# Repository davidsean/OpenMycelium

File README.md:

# OpenMycelium
Yet another Raspberry Pi project: an IoT environmental controller for mycelium growth and fruiting.
This is a open-hardware and open-source DIY project.
It can be used to control the conditions for spawn incubation, mycelium growth and for fruiting.

# Project status
This is still in its infancy. Nothing works yet, so please join the OpenIoT discord server (https://discord.com/invite/Ft229PDrxF) to contribute.

# Hardware
It comprises of a control board with temperature and humidity sensors, that can actual a heater, fan (and ultrasonic mister), light.
All the sensors and actuators are optional, so you jsut need to buy/assemble what you need.

## GOAL (not done yet)
The KiCAD PCB is provided that takes the form of a Raspberry-pi hat.
It needs be populate with some through-hole components (so find someone with a soldering iron if you aren't sure of being able to do this).
The PCB is more or less modular so you dpn't need to fully assemble it with all the features if you don't need them.

# Sofware
The software runs on a Raspberry-Pi.

## Goal (not done yet)
Uses cloud-link to host a Firebase webserver as an interface.
Logs telemetry over MQTT, can choose control "growth recipes".

# dev
```bash
conda create -n openmycelium python=3.8
conda activate openmycelium
python3 -m pip install -r requirements.txt
```

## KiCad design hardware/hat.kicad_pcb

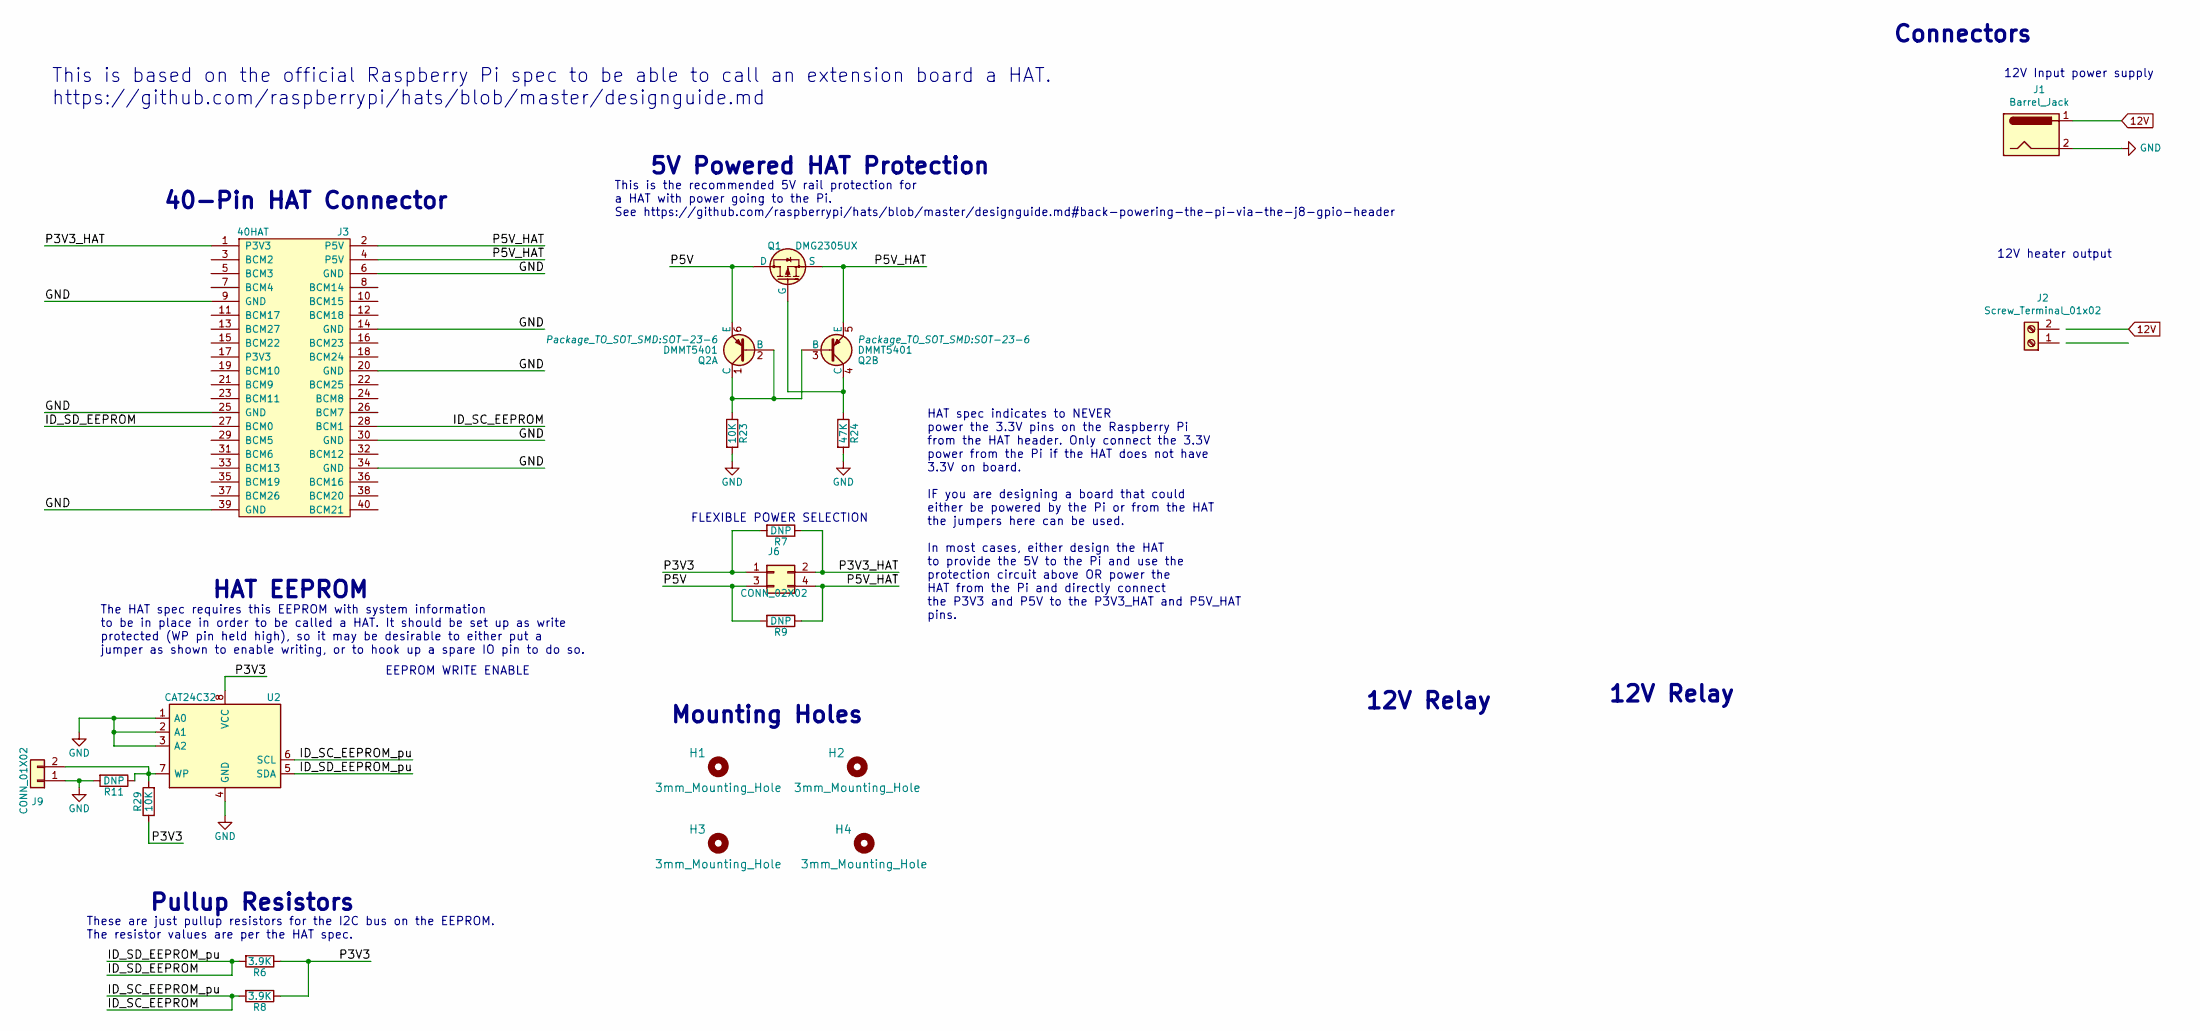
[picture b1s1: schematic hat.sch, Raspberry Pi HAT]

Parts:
H1, H2, H3, H4: 3mm_Mounting_Hole; NPTH_3mm_ID
J1: Barrel_Jack; BarrelJack_Horizontal
J2: Screw_Terminal_01x02; TerminalBlock_4Ucon_1x02_P3.50mm_Horizontal
J3: 40HAT; PinSocket_2x20_P2.54mm_Vertical
J6: CONN_02X02; PinHeader_2x02_P2.54mm_Vertical
J9: CONN_01X02; PinHeader_1x02_P2.54mm_Vertical
Q1: DMG2305UX; SOT-23
Q2: DMMT5401; SOT-23-6
R6, R8: 3.9K; R_0603_1608Metric_Pad0.84x1.00mm_HandSolder
R7, R9, R11: DNP; R_0603_1608Metric_Pad0.84x1.00mm_HandSolder
R23, R29: 10K; R_0603_1608Metric_Pad0.84x1.00mm_HandSolder
R24: 47K; R_0603_1608Metric_Pad0.84x1.00mm_HandSolder
U2: CAT24C32; SOIC-8_3.9x4.9mm_P1.27mm

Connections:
12V: J1.1
/ID_SC_EEPROM: J3.28 (BCM1), R8.2, U2.6 (SCL)
/ID_SD_EEPROM: J3.27 (BCM0), R6.2, U2.5 (SDA)
/P3V3: J6.1, R6.1, R7.2, R8.1, R29.1, U2.8 (VCC)
/P3V3_HAT: J3.1 (P3V3), J6.2, R7.1
/P5V: J6.3, Q1.3 (D), Q2.6 (E), R9.2
/P5V_HAT: J3.2 (P5V), J3.4 (P5V), J6.4, Q1.2 (S), Q2.5 (E), R9.1
GND: J1.2, J3.6 (GND), J3.9 (GND), J3.14 (GND), J3.20 (GND), J3.25 (GND), J3.30 (GND), J3.34 (GND), J3.39 (GND), J9.1, R11.2, R23.2, R24.2, U2.1 (A0), U2.2 (A1), U2.3 (A2), U2.4 (GND)
unnamed: J9.2, R11.1, R29.2, U2.7 (WP)
unnamed: Q1.1 (G), Q2.4 (C), R24.1
unnamed: Q2.1 (C), Q2.2 (B), Q2.3 (B), R23.1

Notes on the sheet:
FLEXIBLE POWER SELECTION
5V Powered HAT Protection
This is the recommended 5V rail protection for a HAT with power going to the Pi. See https://github.com/raspberrypi/hats/blob/master/designguide.md#back-powering-the-pi-via-the-j8-gpio-header
EEPROM WRITE ENABLE
Pullup Resistors
HAT EEPROM
Mounting Holes
40-Pin HAT Connector
HAT spec indicates to NEVER power the 3.3V pins on the Raspberry Pi from the HAT header. Only connect the 3.3V power from the Pi if the HAT does not have 3.3V on board. IF you are designing a board that could either be powered by the Pi or from the HAT the jumpers here can be used. In most cases, e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
The HAT spec requires this EEPROM with system information to be in place in order to be called a HAT. It should be set up as write protected (WP pin held high), so it may be desirable to either put a jumper as shown to enable writing, or to hook up a spare IO pin to do so.
These are just pullup resistors for the I2C bus on the EEPROM. The resistor values are per the HAT spec.
This is based on the official Raspberry Pi spec to be able to call an extension board a HAT. https://github.com/raspberrypi/hats/blob/master/designguide.md
12V Relay
Connectors
12V heater output
12V Input power supply

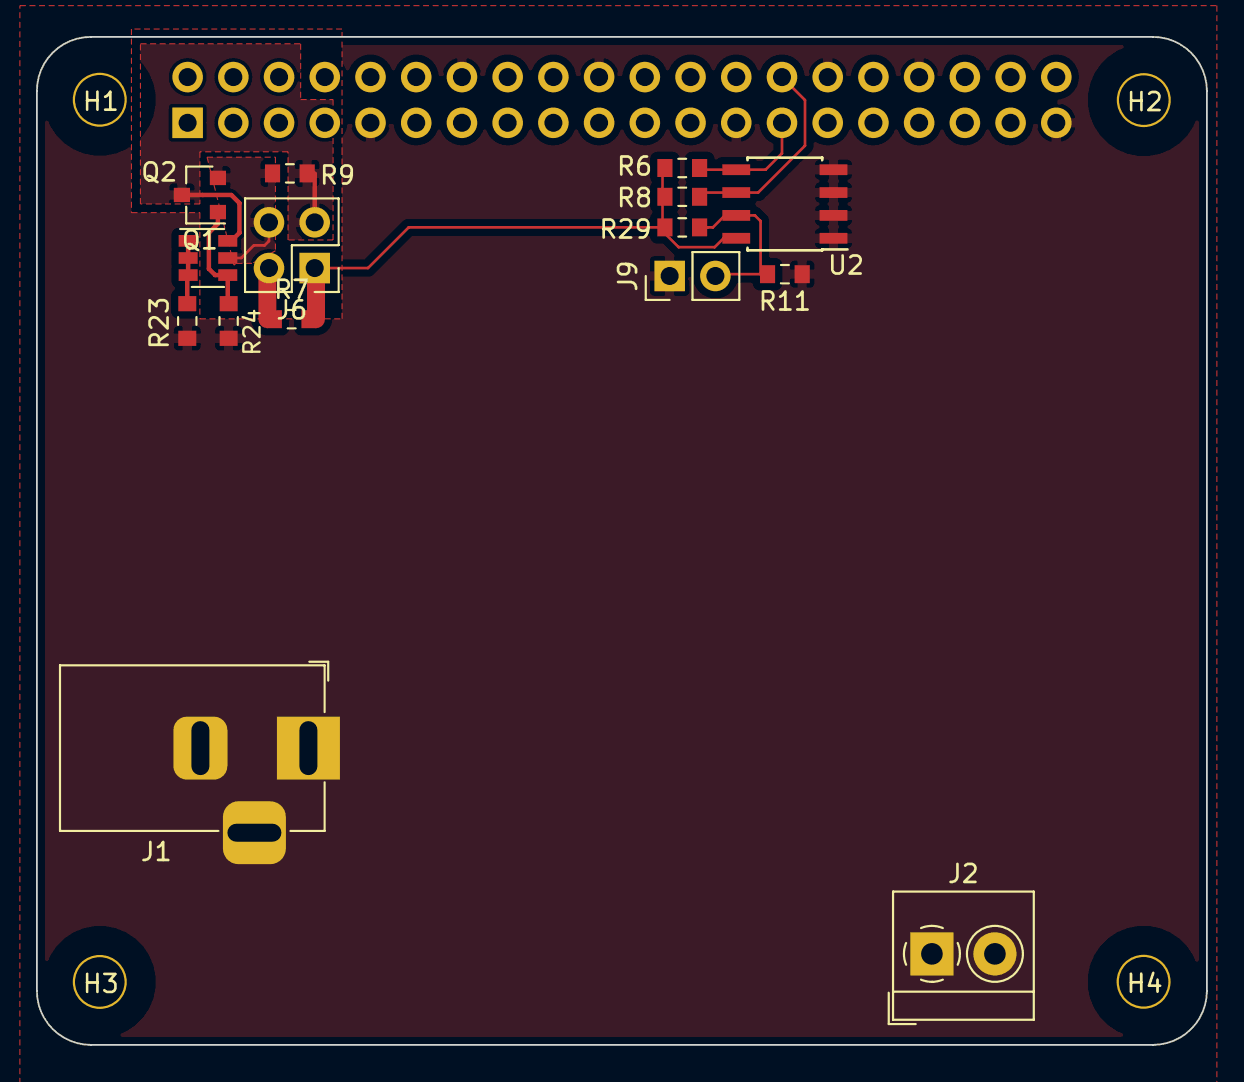
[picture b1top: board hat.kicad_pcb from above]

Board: 4 copper layers, 65.0 x 56.0 mm, 20 parts (1 on the bottom side), 10 nets.

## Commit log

2021-04-18 add cloud-link submodule
2021-04-18 add rpi hat from KiCad template
2021-04-19 update an test GH webhook
